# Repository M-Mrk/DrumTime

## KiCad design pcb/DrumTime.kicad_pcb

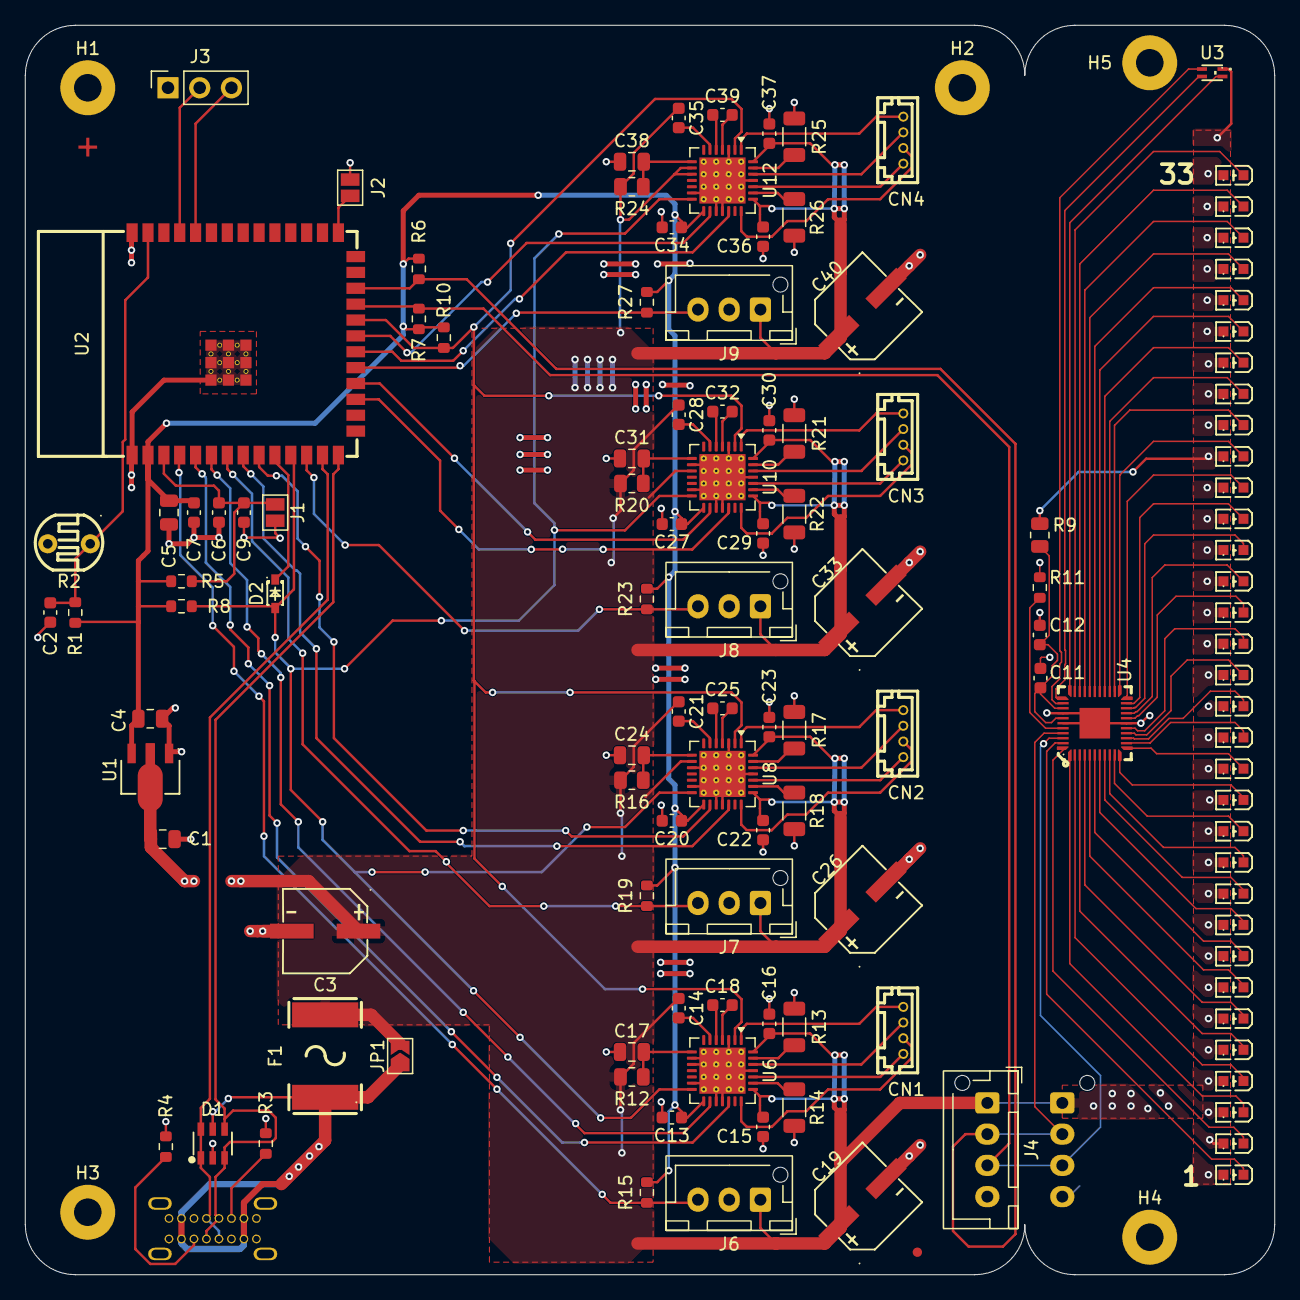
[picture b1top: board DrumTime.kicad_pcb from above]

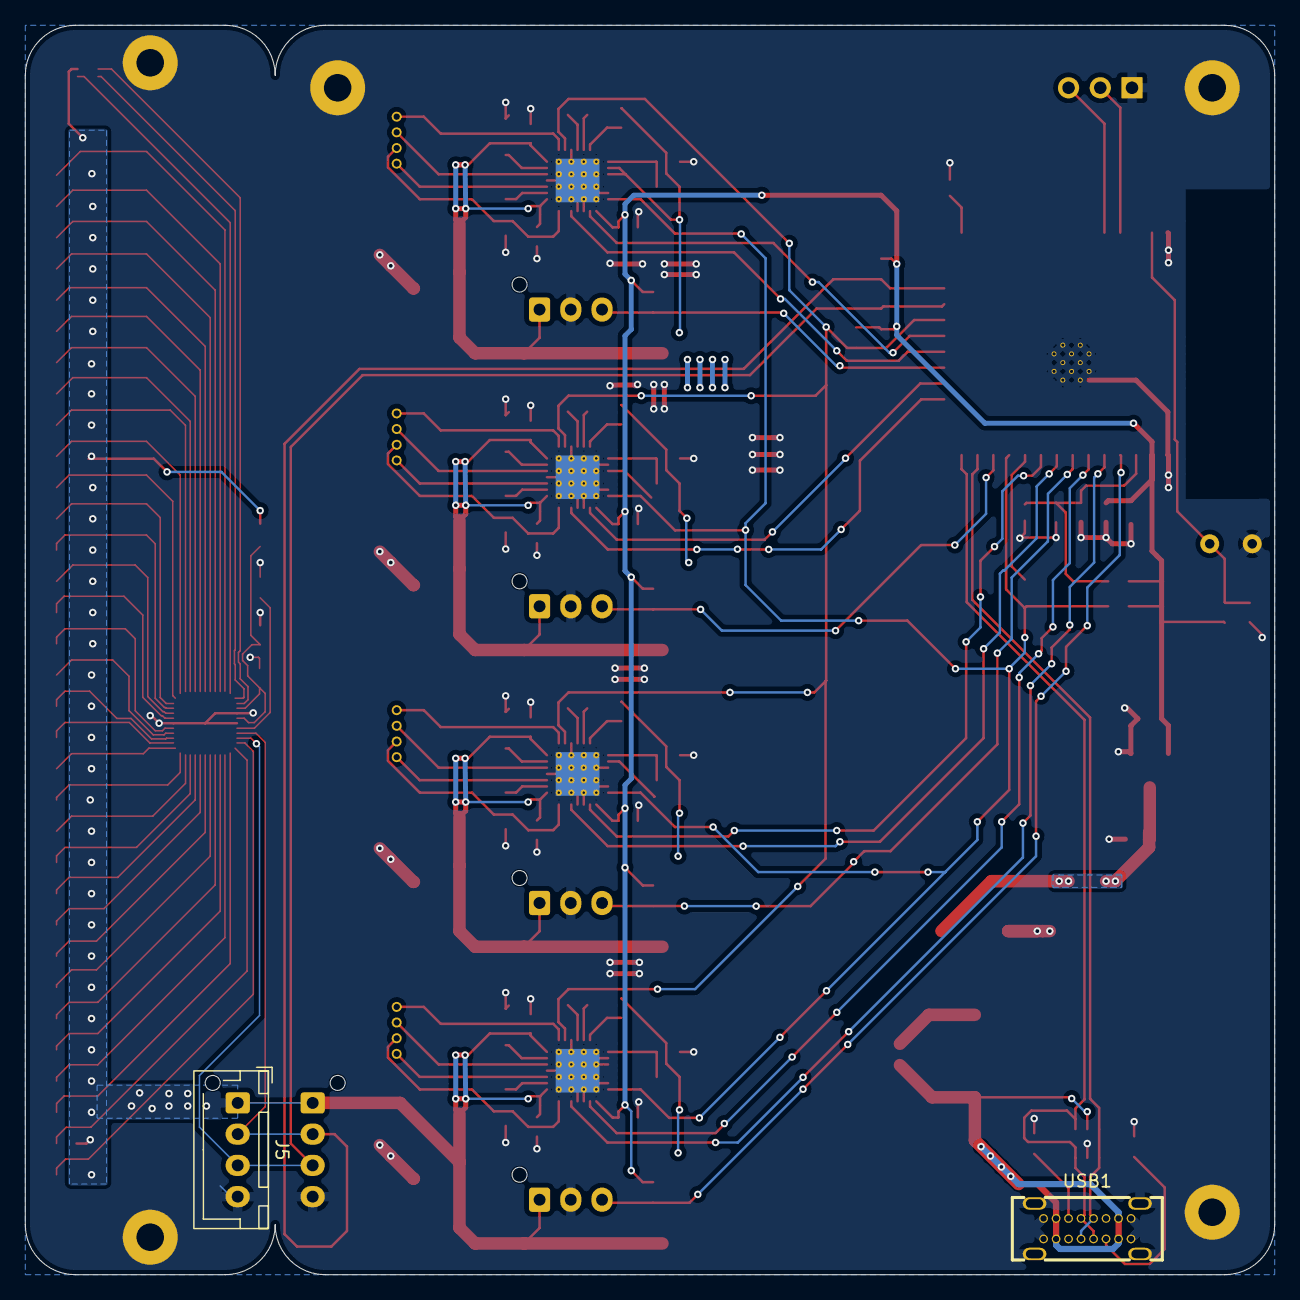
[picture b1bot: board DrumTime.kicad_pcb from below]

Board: 2 copper layers, 100.0 x 100.0 mm, 131 parts (2 on the bottom side), 108 nets.

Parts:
C1, C4, C17, C24, C31, C38: 10uF; C_0805_2012Metric
C2, C6, C7, C11, C13, C14, C15, C16, C20, C21, C22, C23, C27, C28, C29, C30, C34, C35, C36, C37: 100nF; C_0603_1608Metric
C3, C19, C26, C33, C40: 100uF; CAP-SMD_BD6.3-L6.6-W6.6-FD
C5: 22uF; C_0805_2012Metric
C9, C12: 1uF; C_0603_1608Metric
C18, C25, C32, C39: 22nF; C_0603_1608Metric
CN1, CN2, CN3, CN4: Motor; CONN-TH_530470410
D1: USBLC6-2SC6; SOT-23-6_L2.9-W1.6-P0.95-LS2.8-BL
D2: BAT60B; SOD-323_L1.7-W1.3-LS2.6-RD-1
F1: Polyfuse; F2920
FID1: Fiducial; Fiducial_Cross_1.5mm_Mask2mm
FID2: Fiducial; Fiducial_0.75mm_Mask1.5mm
H1, H2, H3, H4, H5: MountingHole; MountingHole_2.2mm_M2_Pad
J1: EN; SolderJumper-2_P1.3mm_Open_Pad1.0x1.5mm
J2: Boot; SolderJumper-2_P1.3mm_Open_Pad1.0x1.5mm
J3: Debug; PinSocket_1x03_P2.54mm_Vertical
J4, J5: LED_Conn; JST_XH_B4B-XH-AM_1x04_P2.50mm_Vertical
J6, J7, J8, J9: Hall; JST_XH_B3B-XH-AM_1x03_P2.50mm_Vertical
JP1: JMP Fuse; SolderJumper-2_P1.3mm_Open_TrianglePad1.0x1.5mm
LED1, LED2, LED3, LED4, LED5, LED6, LED7, LED8, LED9, LED10, LED11, LED12, LED13, LED14, LED15, LED16, LED17, LED18, LED19, LED20, LED21, LED22, LED23, LED24, LED25, LED26, LED27, LED28, LED29, LED30, LED31, LED32, LED33: LED0603-R-RD_WHITE
R1, R5, R10, R15, R19, R23, R27: 10kR; R_0603_1608Metric
R2: GL5528; RES-TH_L5.1-W4.3-P3.40-D0.5
R3, R4, R6, R7, R8: 5.1kR; R_0603_1608Metric
R9, R12, R16, R20, R24: 10R; R_0805_2012Metric
R11: 15kR; R_0603_1608Metric
R13, R14, R17, R18, R21, R22, R25, R26: 0.33R; R_1206_3216Metric
U1: ME6210A33PG; SOT-89_L4.5-W2.5-P1.50-LS4.2-BR
U2: ESP32-S3-WROOM-1-N8; WIFIM-SMD_ESP32-S3-WROOM-1-N8
U3: TJ-S1608SW6TDSLCCYRGB-A5; LED-ARRAY-SMD_4P-L1.6-W0.8-BL-FD
U4: IS31FL3236A-QFLS2-TR; QFN-44_L5.0-W5.0-P0.40-BL-EP
U6, U8, U10, U12: TMC2209-LA; VQFN-28-1EP_5x5mm_P0.5mm_EP3.7x3.7mm_ThermalVias
USB1: Type-C; USB-C-TH_TYPE-C16PLCH10.0-B143

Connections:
+3V3: C4.1, C5.1, C7.1, C13.1, C20.1, C27.1, C34.1, R1.2, R5.1, R6.1, R7.1, R8.1, R10.1, R15.1, R19.1, R23.1, R27.1, U1.3 (Vout), U2.2 (3V3), U6.15 (VCC_IO), U8.15 (VCC_IO), U10.15 (VCC_IO), U12.15 (VCC_IO)
+5V: C1.1, C3.1, C14.1, C15.1, C16.1, C19.1, C21.1, C22.1, C23.1, C26.1, C28.1, C29.1, C30.1, C33.1, C35.1, C36.1, C37.1, C40.1, F1.2, J4.1, J5.1, J6.1, J7.1, J8.1, J9.1, JP1.2 (B), LED1.1 (A), LED2.1 (A), LED3.1 (A), LED4.1 (A), LED5.1 (A), LED6.1 (A), LED7.1 (A), LED8.1 (A), LED9.1 (A), LED10.1 (A), LED11.1 (A), LED12.1 (A), LED13.1 (A), LED14.1 (A), LED15.1 (A), LED16.1 (A), LED17.1 (A), LED18.1 (A), LED19.1 (A), LED20.1 (A), LED21.1 (A), LED22.1 (A), LED23.1 (A), LED24.1 (A), LED25.1 (A), LED26.1 (A), LED27.1 (A), LED28.1 (A), LED29.1 (A), LED30.1 (A), LED31.1 (A), LED32.1 (A), LED33.1 (A), R9.1, R12.1, R16.1, R20.1, R24.1, U1.2 (Vin), U3.1 (+), U6.22 (VS), U6.28 (VS), U8.9 (MS1/AD0), U8.22 (VS), U8.28 (VS), U10.10 (MS2/AD1), U10.22 (VS), U10.28 (VS), U12.9 (MS1/AD0), U12.10 (MS2/AD1), U12.22 (VS), U12.28 (VS)
/LDR_sense: C2.1, R1.1, R2.1, U2.39 (IO1)
/LEDs/1: LED1.2 (K), U4.43 (OUT1)
/LEDs/2: LED2.2 (K), U4.44 (OUT2)
/LEDs/3: LED3.2 (K), U4.1 (OUT3)
/LEDs/4: LED4.2 (K), U4.2 (OUT4)
/LEDs/5: LED5.2 (K), U4.3 (OUT5)
/LEDs/6: LED6.2 (K), U4.4 (OUT6)
/LEDs/7: LED7.2 (K), U4.5 (OUT7)
/LEDs/8: LED8.2 (K), U4.6 (OUT8)
/LEDs/9: LED9.2 (K), U4.7 (OUT9)
/LEDs/10: LED10.2 (K), U4.8 (OUT10)
/LEDs/11: LED11.2 (K), U4.9 (OUT11)
/LEDs/12: LED12.2 (K), U4.10 (OUT12)
/LEDs/13: LED13.2 (K), U4.11 (OUT13)
/LEDs/14: LED14.2 (K), U4.12 (OUT14)
/LEDs/15: LED15.2 (K), U4.13 (OUT15)
/LEDs/16: LED16.2 (K), U4.14 (OUT16)
/LEDs/17: LED17.2 (K), U4.15 (OUT17)
/LEDs/18: LED18.2 (K), U4.16 (OUT18)
/LEDs/19: LED19.2 (K), U4.18 (OUT19)
/LEDs/20: LED20.2 (K), U4.19 (OUT20)
/LEDs/21: LED21.2 (K), U4.20 (OUT21)
/LEDs/22: LED22.2 (K), U4.21 (OUT22)
/LEDs/23: LED23.2 (K), U4.22 (OUT23)
/LEDs/24: LED24.2 (K), U4.23 (OUT24)
/LEDs/25: LED25.2 (K), U4.24 (OUT25)
/LEDs/26: LED26.2 (K), U4.25 (OUT26)
/LEDs/27: LED27.2 (K), U4.26 (OUT27)
/LEDs/28: LED28.2 (K), U4.27 (OUT28)
/LEDs/29: LED29.2 (K), U4.28 (OUT29)
/LEDs/30: LED30.2 (K), U4.29 (OUT30)
/LEDs/31: LED31.2 (K), U4.30 (OUT31)
/LEDs/32: LED32.2 (K), U4.31 (OUT32)
/LEDs/33: LED33.2 (K), U4.32 (OUT33)
/Motor1/A+: CN2.1, U8.24 (OA1)
/Motor1/A-: CN2.2, U8.21 (OA2)
/Motor1/B+: CN2.3, U8.26 (OB1)
/Motor1/B-: CN2.4, U8.1 (OB2)
/Motor2/A+: CN3.1, U10.24 (OA1)
/Motor2/A-: CN3.2, U10.21 (OA2)
/Motor2/B+: CN3.3, U10.26 (OB1)
/Motor2/B-: CN3.4, U10.1 (OB2)
/Motor3/A+: CN4.1, U12.24 (OA1)
/Motor3/A-: CN4.2, U12.21 (OA2)
/Motor3/B+: CN4.3, U12.26 (OB1)
/Motor3/B-: CN4.4, U12.1 (OB2)
/Motor/A+: CN1.1, U6.24 (OA1)
/Motor/A-: CN1.2, U6.21 (OA2)
/Motor/B+: CN1.3, U6.26 (OB1)
/Motor/B-: CN1.4, U6.1 (OB2)
/RGB_B: U3.2 (-), U4.35 (OUT36)
/RGB_G: U3.3 (-), U4.34 (OUT35)
/RGB_R: U3.4 (-), U4.33 (OUT34)
/SCL: J4.3, J5.3, R7.2, U2.23 (IO21), U4.42 (SCL)
/SDA: J4.2, J5.2, R6.2, U2.24 (IO47), U4.41 (SDA)
/SDB: C11.1, C12.1, R9.2, U4.36 (SDB), U4.38 (VCC)
/USB_D+: D1.3, D1.4, U2.14 (IO20), USB1.A6 (DP1), USB1.B6 (DP2)
/USB_D-: D1.1, D1.6, U2.13 (IO19), USB1.A7 (DN1), USB1.B7 (DN2)
/cc1: R3.1, USB1.A5 (CC1)
/cc2: R4.1, USB1.B5 (CC2)
/m0_dir: U2.5 (IO5), U6.19 (DIR)
/m0_hall: J6.3, R15.2, U2.4 (IO4)
/m0_step: U2.6 (IO6), U6.16 (STEP)
/m1_dir: U2.8 (IO15), U8.19 (DIR)
/m1_hall: J7.3, R19.2, U2.7 (IO7)
/m1_step: U2.9 (IO16), U8.16 (STEP)
/m2_dir: U2.17 (IO9), U10.19 (DIR)
/m2_hall: J8.3, R23.2, U2.12 (IO8)
/m2_step: U2.18 (IO10), U10.16 (STEP)
/m3_dir: U2.20 (IO12), U12.19 (DIR)
/m3_hall: J9.3, R27.2, U2.19 (IO11)
/m3_step: U2.21 (IO13), U12.16 (STEP)
/m_enn: R10.2, U2.22 (IO14), U6.2 (~EN), U8.2 (~EN), U10.2 (~EN), U12.2 (~EN)
/m_uart: D2.2 (A), R8.2, U2.11 (IO18), U6.14 (~PD/UART), U8.14 (~PD/UART), U10.14 (~PD/UART), U12.14 (~PD/UART)
/uart1_tx: D2.1 (K), U2.10 (IO17)
GND: C1.2, C2.2, C3.2, C4.2, C5.2, C6.2, C7.2, C9.2, C11.2, C12.2, C13.2, C15.2, C16.2, C17.1, C19.2, C20.2, C22.2, C23.2, C24.1, C26.2, C27.2, C29.2, C30.2, C31.1, C33.2, C34.2, C36.2, C37.2, C38.1, C40.2, D1.2, H1.1 (1_1), H2.1 (1_1), H3.1 (1_1), H4.1 (1_1), H5.1 (1_1), J1.2, J2.2, J3.1, J4.4, J5.4, J6.2, J7.2, J8.2, J9.2, R2.2, R3.2, R4.2, R11.2, R13.2, R14.2, R17.2, R18.2, R21.2, R22.2, R25.2, R26.2, U1.1 (Vss), U2.1 (GND), U2.40 (GND), U2.41 (EP), U4.17 (GND), U4.37 (AD), U4.39 (GND), U4.45 (EPAD), U6.3 (GND), U6.9 (MS1/AD0), U6.10 (MS2/AD1), U6.13 (CLK), U6.17 (VREF), U6.18 (GND), U6.25 (NC), U6.29 (GND), U8.3 (GND), U8.10 (MS2/AD1), U8.13 (CLK), U8.17 (VREF), U8.18 (GND), U8.25 (NC), U8.29 (GND), U10.3 (GND), U10.9 (MS1/AD0), U10.13 (CLK), U10.17 (VREF), U10.18 (GND), U10.25 (NC), U10.29 (GND), U12.3 (GND), U12.13 (CLK), U12.17 (VREF), U12.18 (GND), U12.25 (NC), U12.29 (GND), USB1.0 (EH), USB1.A1 (GND), USB1.A12 (GND), USB1.B1 (GND), USB1.B12 (GND)
unnamed: C6.1, C9.1, J1.1, R5.2, U2.3 (EN)
unnamed: J2.1, U2.27 (IO0)
unnamed: J3.2, U2.37 (TXD0)
unnamed: J3.3, U2.36 (RXD0)
unnamed: R11.1, U4.40 (R-EXT)
unnamed: C17.2, R12.2, U6.8 (5VOUT)
unnamed: R14.1, U6.23 (BRA)
unnamed: R13.1, U6.27 (BRB)
unnamed: C18.2, U6.5 (CPI)
unnamed: C18.1, U6.4 (CPO)
unnamed: C14.2, U6.6 (VCP)
unnamed: C24.2, R16.2, U8.8 (5VOUT)
unnamed: R18.1, U8.23 (BRA)
unnamed: R17.1, U8.27 (BRB)
unnamed: C25.2, U8.5 (CPI)
unnamed: C25.1, U8.4 (CPO)
unnamed: C21.2, U8.6 (VCP)
unnamed: C31.2, R20.2, U10.8 (5VOUT)
unnamed: R22.1, U10.23 (BRA)
unnamed: R21.1, U10.27 (BRB)
unnamed: C32.2, U10.5 (CPI)
unnamed: C32.1, U10.4 (CPO)
unnamed: C28.2, U10.6 (VCP)
unnamed: C38.2, R24.2, U12.8 (5VOUT)
unnamed: R26.1, U12.23 (BRA)
unnamed: R25.1, U12.27 (BRB)
unnamed: C39.2, U12.5 (CPI)
unnamed: C39.1, U12.4 (CPO)
unnamed: C35.2, U12.6 (VCP)
VBUS: D1.5, F1.1, JP1.1 (A), USB1.A4 (VBUS), USB1.A9 (VBUS), USB1.B4 (VBUS), USB1.B9 (VBUS)

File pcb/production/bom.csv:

Designator,Footprint,Quantity,Value,LCSC Part #
"C1, C17, C24, C31, C38, C4",0805,6,10uF,C15850
"C11, C13, C14, C15, C16, C2, C20, C21, C22, C23, C27, C28, C29, C30, C34, C35, C36, C37, C6, C7",0603,20,100nF,C14663
"C12, C9",0603,2,1uF,C15849
"C18, C25, C32, C39",0603,4,22nF,C21122
"C19, C26, C3, C33, C40",CAP-SMD_BD6.3-L6.6-W6.6-FD,5,100uF,C320569
C5,0805,1,22uF,C45783
"CN1, CN2, CN3, CN4",CONN-TH_530470410,4,Motor,C504989
D1,SOT-23-6_L2.9-W1.6-P0.95-LS2.8-BL,1,USBLC6-2SC6,C7519
D2,SOD-323_L1.7-W1.3-LS2.6-RD-1,1,BAT60B,C7502695
F1,F2920,1,Polyfuse,C21009
"J4, J5",JST_XH_B4B-XH-AM_1x04_P2.50mm_Vertical,2,LED_Conn,
"J6, J7, J8, J9",JST_XH_B3B-XH-AM_1x03_P2.50mm_Vertical,4,Hall,
"LED1, LED10, LED11, LED12, LED13, LED14, LED15, LED16, LED17, LED18, LED19, LED2, LED20, LED21, LED22, LED23, LED24, LED25, LED26, LED27, LED28, LED29, LED3, LED30, LED31, LED32, LED33, LED4, LED5, LED6, LED7, LED8, LED9",LED0603-R-RD_WHITE,33,~,C2290
"R1, R10, R15, R19, R23, R27, R5",0603,7,10kR,C25804
R11,0603,1,15kR,C2906995
"R12, R16, R20, R24, R9",0805,5,10R,C17415
"R13, R14, R17, R18, R21, R22, R25, R26",1206,8,0.33R,C2907351
R2,RES-TH_L5.1-W4.3-P3.40-D0.5,1,GL5528,C10081
"R3, R4, R6, R7, R8",0603,5,5.1kR,C23186
U1,SOT-89_L4.5-W2.5-P1.50-LS4.2-BR,1,ME6210A33PG,C85233
"U10, U12, U6, U8",VQFN-28-1EP_5x5mm_P0.5mm_EP3.7x3.7mm_ThermalVias,4,TMC2209-LA,C2150710
U2,WIFIM-SMD_ESP32-S3-WROOM-1-N8,1,ESP32-S3-WROOM-1-N8,C2913198
U3,LED-ARRAY-SMD_4P-L1.6-W0.8-BL-FD,1,TJ-S1608SW6TDSLCCYRGB-A5,C5356078
U4,QFN-44_L5.0-W5.0-P0.40-BL-EP,1,IS31FL3236A-QFLS2-TR,C246443
USB1,USB-C-TH_TYPE-C16PLCH10.0-B143,1,Type-C,C49261586
